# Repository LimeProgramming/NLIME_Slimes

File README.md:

> [!WARNING]
> This has not been made ***yet*** so not confirmed working. While you're free to make it anyway, do not blame me if it doesn't work. You have been warned.

## NLIME_Slimes
SMOL Slime VR trackers based around nRF52840, intended to be similar form factor to commercial Slimes but smaller.

I kinda like them. 

TODO: Write a proper read me maybe later. 

> [!NOTE]
> This was made with KICAD 9 and for some reason opening this project with KICAD 8 corrupts the PCB file.

> [!NOTE]
> Weird print settings
> 0.48 mm wall thickness
> layer 1 height 0.3mm
> layer height 0.26mm

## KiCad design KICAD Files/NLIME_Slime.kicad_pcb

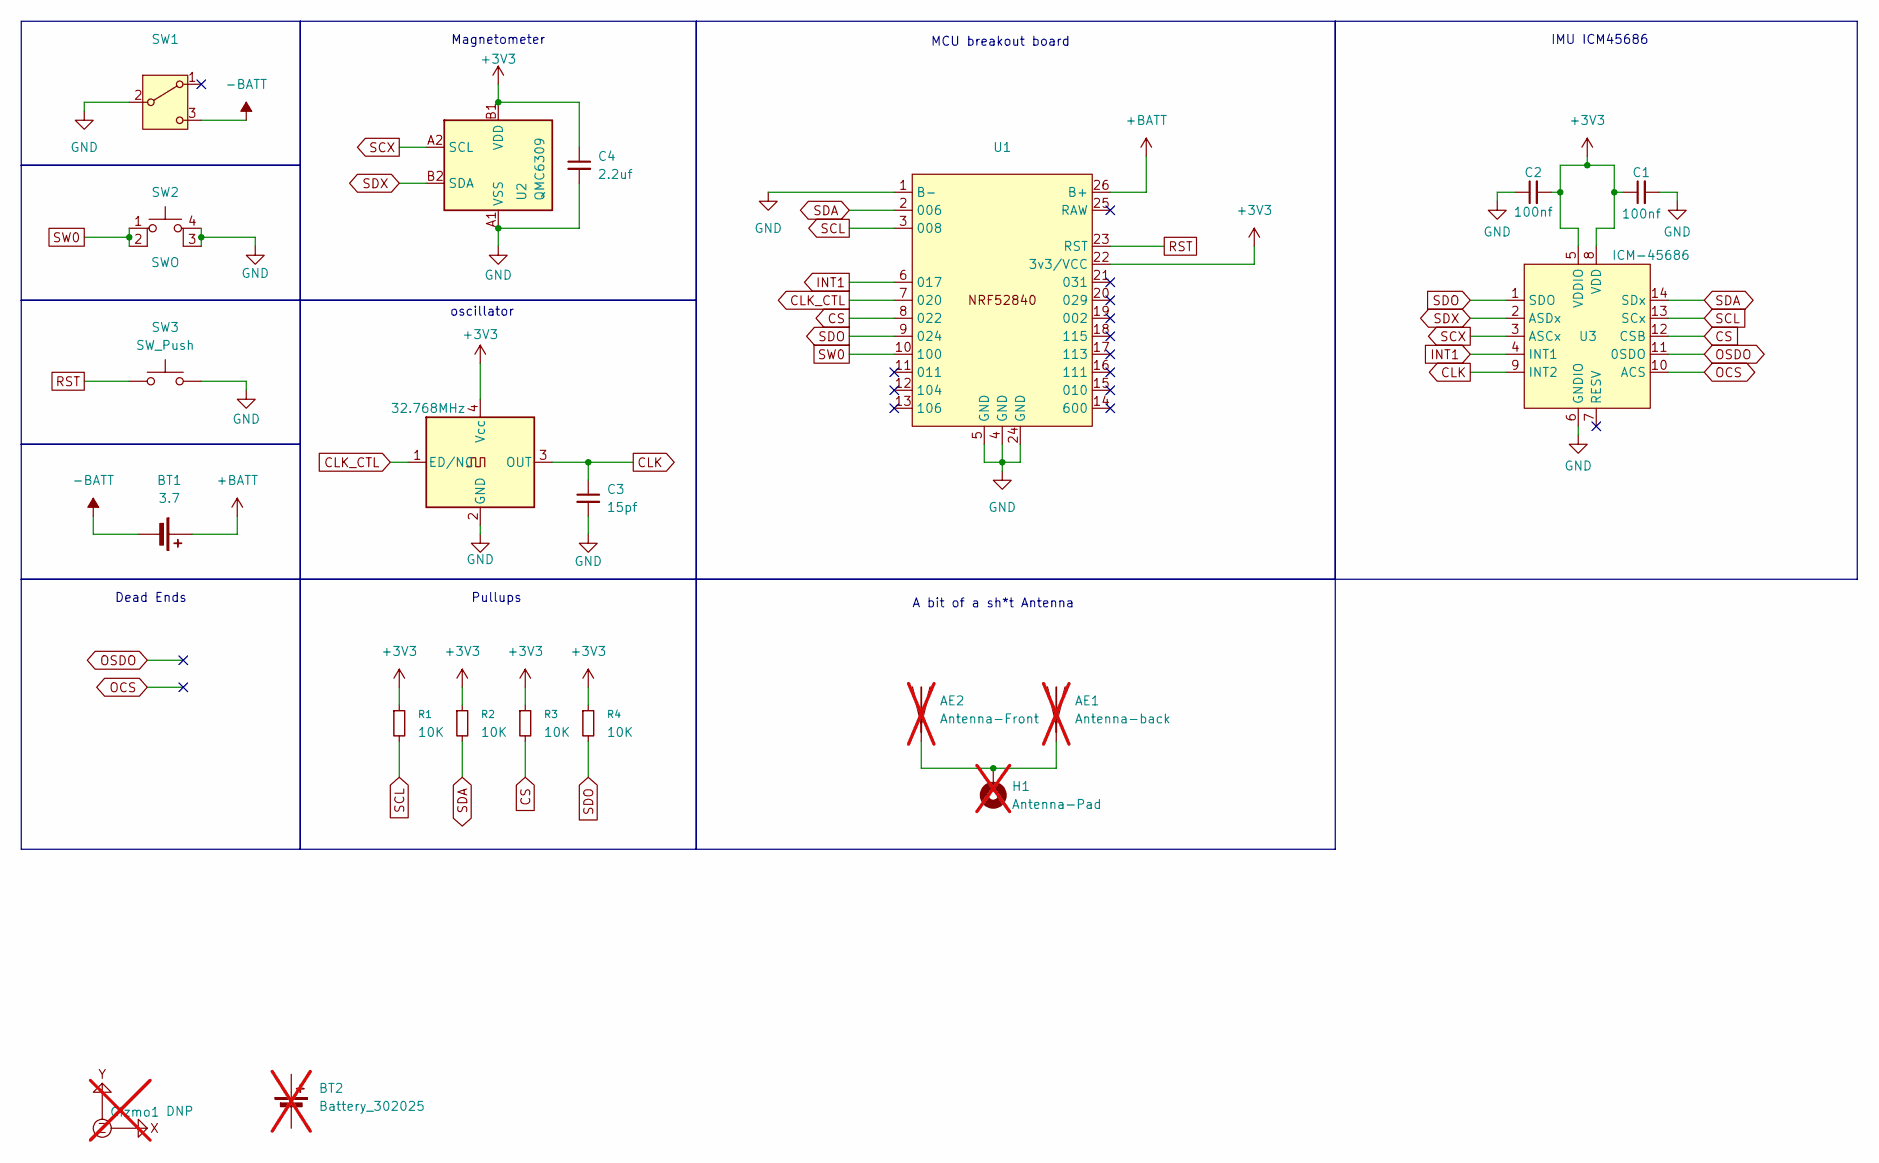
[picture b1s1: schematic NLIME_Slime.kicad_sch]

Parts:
AE1: Antenna-back; Antenna-Strip; not fitted
AE2: Antenna-Front; Antenna-Strip; not fitted
BT1: 3.7; Battery
BT2: Battery_302025; 302025 Bat Rep; not fitted
C1, C2: 100nf; C_0402_NOD; LCSC C1525
C3: 15pf; C_0402_NOD; LCSC C1548
C4: 2.2uf; C_0603_Rounded; LCSC C23630
Gizmo1: DNP; gizmo; not fitted
H1: Antenna-Pad; not fitted
R1, R2, R3, R4: 10K; R_0402_NOD; LCSC C25744
SW1: SW_Slide_SPDT_Angled_CK_OS102011MA1Q; LCSC C393937
SW2: SWO; SMT_SW; LCSC C318884
SW3: SW_Push; SW_Push_SPST_NO_Alps_SKRK; LCSC C720477
U1: nrf52840_stacked
U2: QMC6309; WLP-4_0.86x0.86mm_P0.4mm; LCSC C5439871
U3: ICM-45686; LGA-14_3x2.5mm_P0.5mm; LCSC C22459454
X1: 32.768MHz; Crystal_SMD_3225-4Pin_3.2x2.5mm; LCSC C454609

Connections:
+3V3: C1.1, C2.2, C4.1, R1.1, R2.1, R3.1, R4.1, U1.22 (3v3/VCC), U2.B1 (VDD), U3.5 (VDDIO), U3.8 (VDD), X1.4 (Vcc)
+BATT: BT1.1 (+), U1.26 (B+)
-BATT: BT1.2 (-), SW1.3 (C)
CLK: C3.1, U3.9 (INT2), X1.3 (OUT)
CLK_CTL: U1.7 (020), X1.1 (ED/NC)
CS: R3.2, U1.8 (022), U3.12 (CSB)
GND: C1.2, C2.1, C3.2, C4.2, SW1.2 (B), SW2.3 (K), SW2.4 (A), SW3.2, U1.1 (B-), U1.4 (GND), U1.5 (GND), U1.24 (GND), U2.A1 (VSS), U3.6 (GNDIO), X1.2 (GND)
INT1: U1.6 (017), U3.4 (INT1)
unnamed: AE1.1 (A), AE2.1 (A), H1.1 (MP)
OCS: U3.10 (ACS)
OSDO: U3.11 (0SDO)
RST: SW3.1, U1.23 (RST)
SCL: R1.2, U1.3 (008), U3.13 (SCx)
SCX: U2.A2 (SCL), U3.3 (ASCx)
SDA: R2.2, U1.2 (006), U3.14 (SDx)
SDO: R4.2, U1.9 (024), U3.1 (SDO)
SDX: U2.B2 (SDA), U3.2 (ASDx)
SW0: SW2.1, SW2.2, U1.10 (100)

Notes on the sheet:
MCU breakout board
oscillator
Pullups
IMU ICM45686
A bit of a sh*t Antenna
Dead Ends
Magnetometer

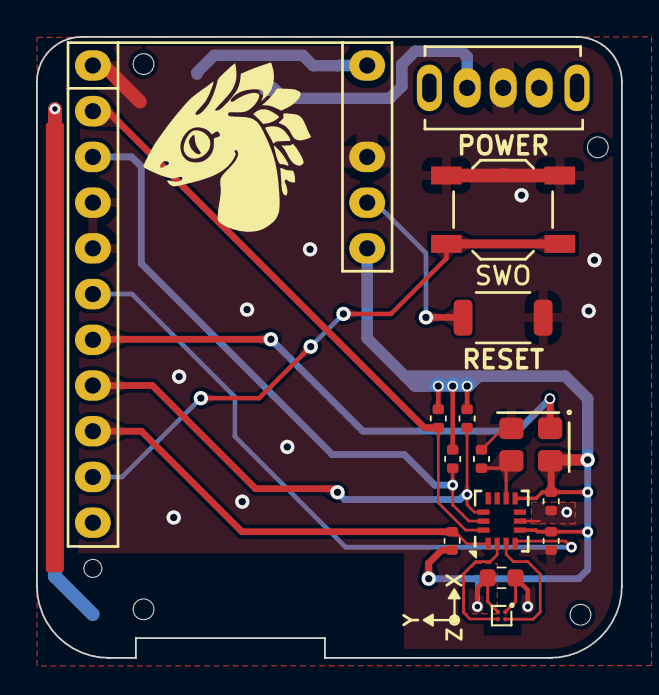
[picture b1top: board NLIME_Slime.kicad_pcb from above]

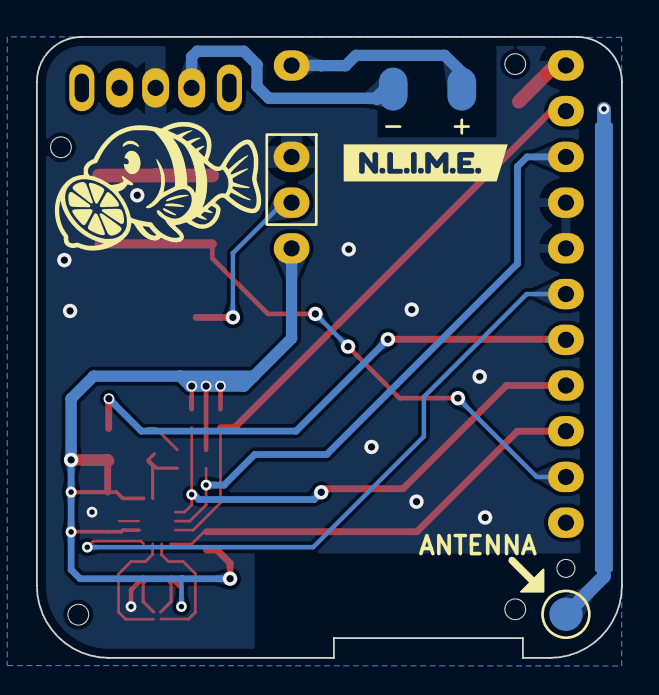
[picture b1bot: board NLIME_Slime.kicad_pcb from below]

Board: 4 copper layers, 32.5 x 34.5 mm, 22 parts (5 on the bottom side), 16 nets.

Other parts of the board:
kibuzzard-68618D06: G***; kibuzzard-68618D06

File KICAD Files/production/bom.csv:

Designator,Footprint,Quantity,Value,LCSC Part #
"C1, C2",C_0402_NOD,2,100nf,C1525
C3,C_0402_NOD,1,15pf,C1548
C4,C_0603_Rounded,1,2.2uf,C12530
"R1, R2, R3, R4",R_0402_NOD,4,10K,C25744
SW1,SW_Slide_SPDT_Angled_CK_OS102011MA1Q,1,~,C393937
SW2,SMT_SW,1,SWO,C318884
SW3,SW_Push_SPST_NO_Alps_SKRK,1,SW_Push,C720477
U2,WLP-4_0.86x0.86mm_P0.4mm,1,QMC6309,C5439871
U3,LGA-14_3x2.5mm_P0.5mm,1,ICM-45686,
X1,Crystal_SMD_3225-4Pin_3.2x2.5mm,1,32.768MHz,C454609

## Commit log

2025-07-07 KICAD FILES UPLOAD 1
2025-08-19 Update LICENSE.MD
    updated to focus on not selling this slime.

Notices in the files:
README.md:
License: Personal Use Only
